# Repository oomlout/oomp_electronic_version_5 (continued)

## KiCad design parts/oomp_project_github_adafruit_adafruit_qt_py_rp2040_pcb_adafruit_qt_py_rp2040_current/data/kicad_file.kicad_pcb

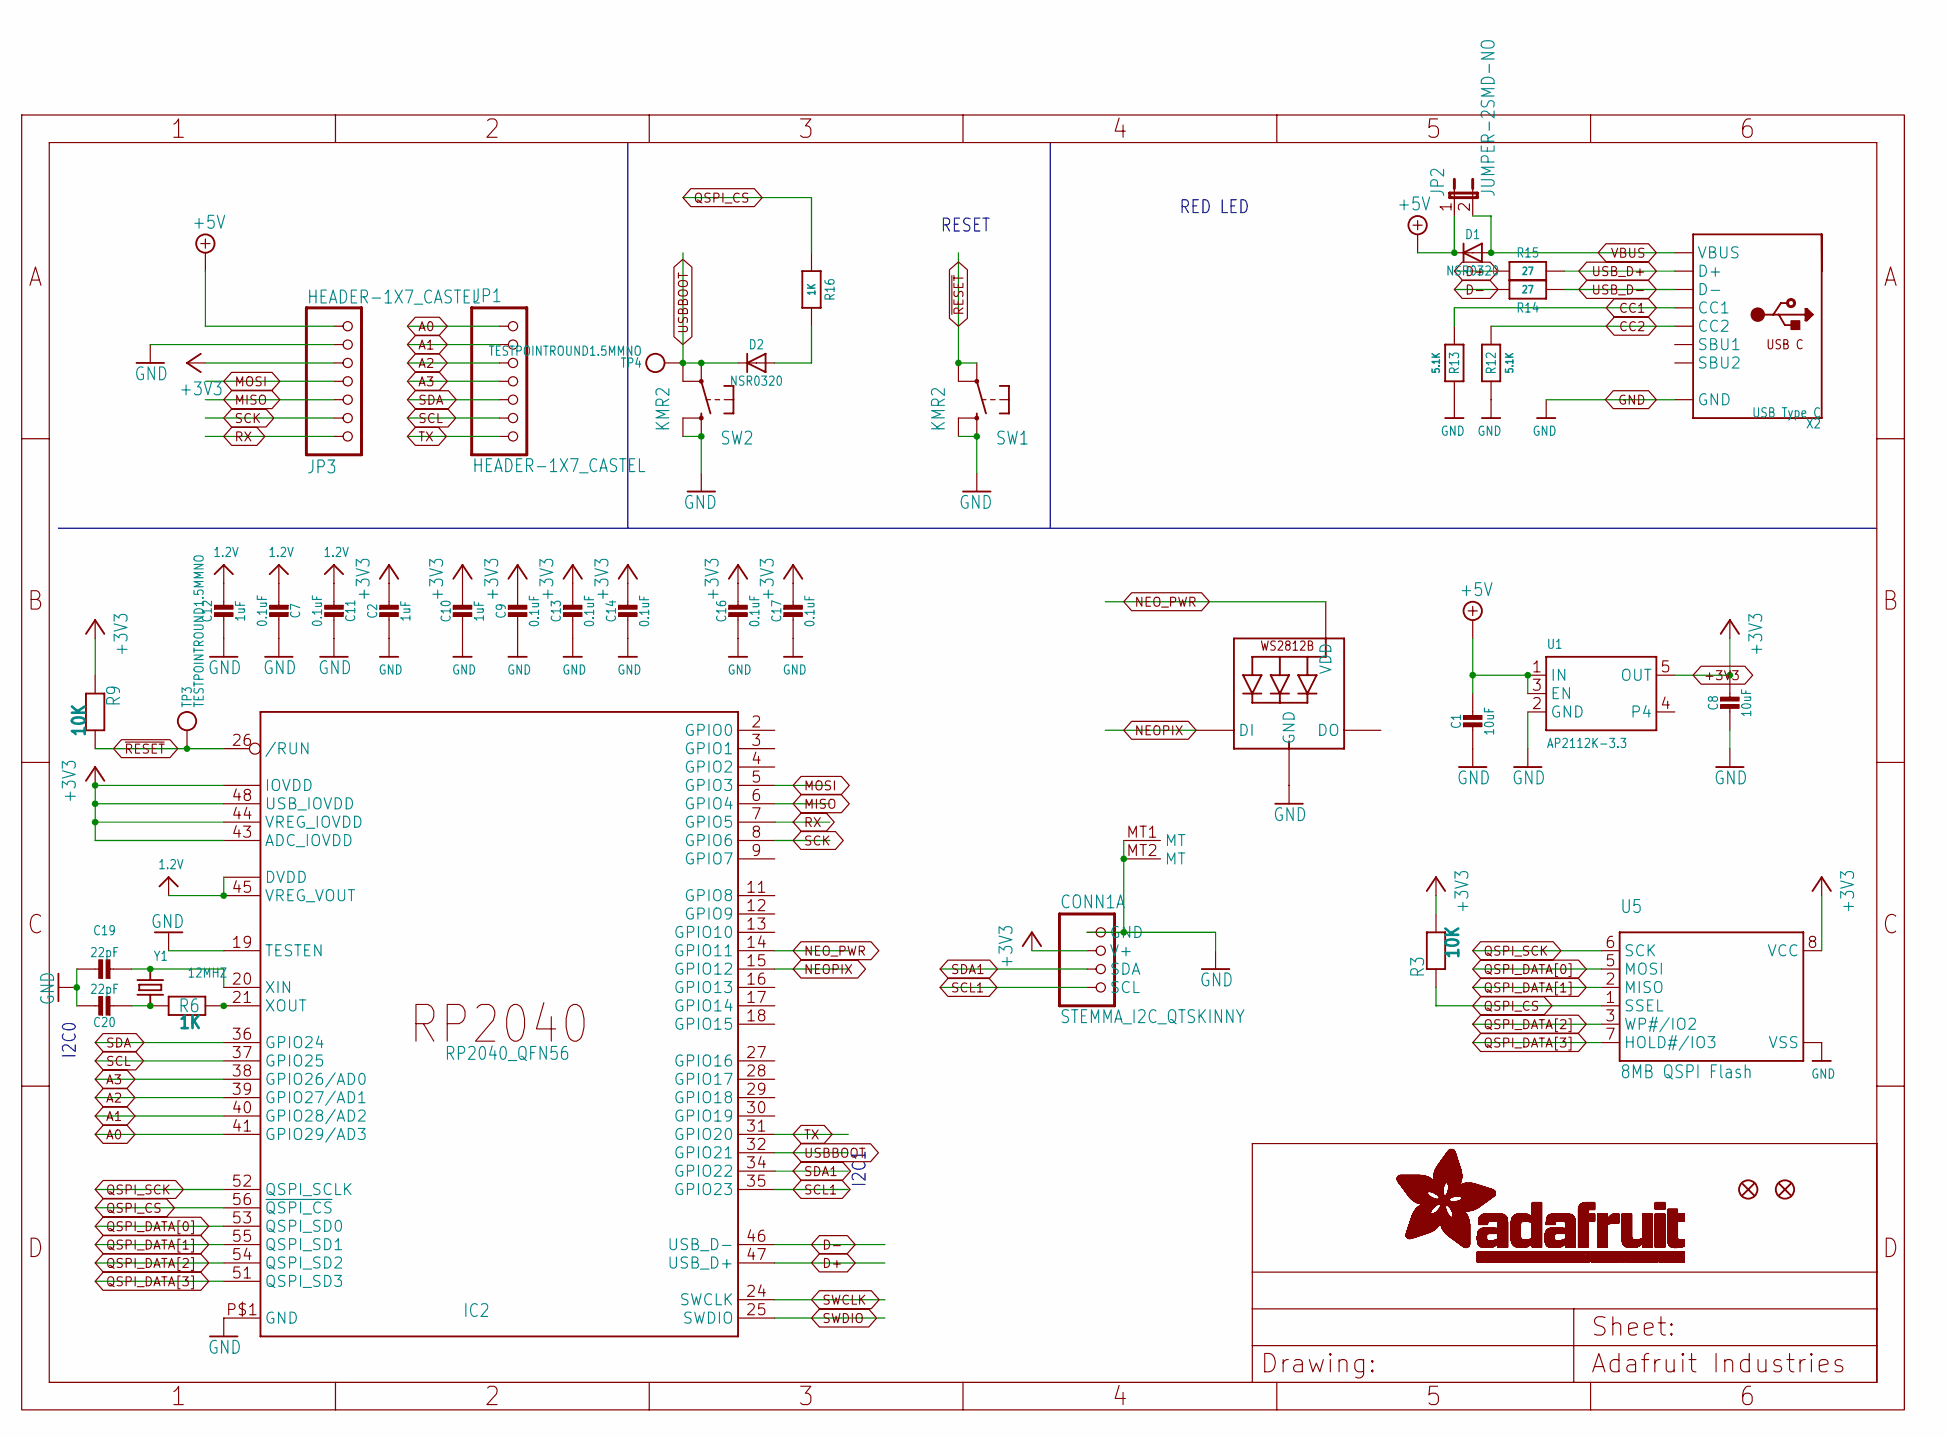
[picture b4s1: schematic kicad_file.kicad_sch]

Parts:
C1, C8: 10uF; 0805-NO
C2, C10, C12: 1uF; 0603-NO
C7, C9, C11, C13, C14, C16, C17: 0.1uF; _0402NO
C19, C20: 22pF; _0402NO
CONN1: STEMMA_I2C_QTSKINNY; JST_SH4_SKINNY
D1, D2: NSR0320; SOD-323_MINI
IC2: RP2040_QFN56; QFN56_7MM_REDUCEDEPAD
JP1, JP3: HEADER-1X7_CASTEL; 1X07_CASTEL
JP2: JUMPER-2SMD-NO; SJ_2S-NO
LED1: WS2812B_SK6805_1515; SK6805_1515
R3, R9: 10K; _0402NO
R6, R16: 1K; _0402NO
R12, R13: 5.1K; _0402NO
R14, R15: 27; _0402NO
SW1, SW2: KMR2; BTN_KMR2_4.6X2.8
TP3, TP4: TESTPOINTROUND1.5MMNO; TESTPOINT_ROUND_1.5MM_NO
U1: AP2112K-3.3; SOT23-5
U5: 8MB QSPI Flash; USON8_4X4
U$6, U$8: FIDUCIAL_1MM
X2: USB Type C; USB_C_CUSB31-CFM2AX-01-X
Y1: 12MHZ; CRYSTAL_2.5X2

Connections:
1.2V: C7.2, C11.2, C12.1, IC2.23 (DVDD), IC2.45 (VREG_VOUT), IC2.50 (DVDD)
+3V3: C2.1, C8.1, C9.1, C10.1, C13.1, C14.1, C16.1, C17.1, CONN1.2 (V+), IC2.1 (IOVDD), IC2.10 (IOVDD), IC2.22 (IOVDD), IC2.33 (IOVDD), IC2.42 (IOVDD), IC2.43 (ADC_IOVDD), IC2.44 (VREG_IOVDD), IC2.48 (USB_IOVDD), IC2.49 (IOVDD), JP3.5, JP3.5C (5), R3.2, R9.1, U1.5 (OUT), U5.8 (VCC)
+5V: C1.1, D1.C, JP2.1, JP3.7, JP3.7C (7), U1.1 (IN), U1.3 (EN)
A0: IC2.41 (GPIO29/AD3), JP1.1, JP1.1C (1)
A1: IC2.40 (GPIO28/AD2), JP1.2, JP1.2C (2)
A2: IC2.39 (GPIO27/AD1), JP1.3, JP1.3C (3)
A3: IC2.38 (GPIO26/AD0), JP1.4, JP1.4C (4)
CC1: R13.2, X2.A5 (CC1)
CC2: R12.2, X2.B5 (CC2)
D+: IC2.47 (USB_D+), R15.2
D-: IC2.46 (USB_D-), R14.2
GND: C1.2, C2.2, C7.1, C8.2, C9.2, C10.2, C11.1, C12.2, C13.2, C14.2, C16.2, C17.2, C19.1, C20.1, CONN1.1 (GND), CONN1.MT1 (MT), CONN1.MT2 (MT), IC2.19 (TESTEN), IC2.P$1 (GND), JP3.6, JP3.6C (6), LED1.4 (GND), R12.1, R13.1, SW1.B (S), SW1.B' (S1), SW2.B (S), SW2.B' (S1), U1.2 (GND), U5.4 (VSS), U5.PAD (VSS), X2.A1B12 (GND), X2.B1A12 (GND)
MISO: IC2.6 (GPIO4), JP3.3, JP3.3C (3)
MOSI: IC2.5 (GPIO3), JP3.4, JP3.4C (4)
unnamed: D2.A, R16.2
unnamed: C19.2, IC2.20 (XIN), Y1.3 (2)
unnamed: C20.2, R6.1, Y1.1
unnamed: IC2.21 (XOUT), R6.2
NEOPIX: IC2.15 (GPIO12), LED1.1 (DI)
NEO_PWR: IC2.14 (GPIO11), LED1.2 (VDD)
QSPI_CS: IC2.56 (~QSPI_CS), R3.1, R16.1, U5.1 (SSEL)
QSPI_DATA[0]: IC2.53 (QSPI_SD0), U5.5 (MOSI)
QSPI_DATA[1]: IC2.55 (QSPI_SD1), U5.2 (MISO)
QSPI_DATA[2]: IC2.54 (QSPI_SD2), U5.3 (WP#/IO2)
QSPI_DATA[3]: IC2.51 (QSPI_SD3), U5.7 (HOLD#/IO3)
QSPI_SCK: IC2.52 (QSPI_SCLK), U5.6 (SCK)
RX: IC2.7 (GPIO5), JP3.1, JP3.1C (1)
SCK: IC2.8 (GPIO6), JP3.2, JP3.2C (2)
SCL: IC2.37 (GPIO25), JP1.6, JP1.6C (6)
SCL1: CONN1.4 (SCL), IC2.35 (GPIO23)
SDA: IC2.36 (GPIO24), JP1.5, JP1.5C (5)
SDA1: CONN1.3 (SDA), IC2.34 (GPIO22)
SWCLK: IC2.24 (SWCLK)
SWDIO: IC2.25 (SWDIO)
TX: IC2.31 (GPIO20), JP1.7, JP1.7C (7)
USBBOOT: D2.C, IC2.32 (GPIO21), SW2.A, SW2.A' (P1), TP4.P$1
USB_D+: R15.1, X2.A6 (D+), X2.B6 (D+)
USB_D-: R14.1, X2.A7 (D-), X2.B7 (D-)
VBUS: D1.A, JP2.2, X2.A4B9 (VBUS), X2.B4A9 (VBUS)
~RESET: IC2.26 (/RUN), R9.2, SW1.A, SW1.A' (P1), TP3.P$1

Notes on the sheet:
I2C0
RESET
RED LED
I2C1

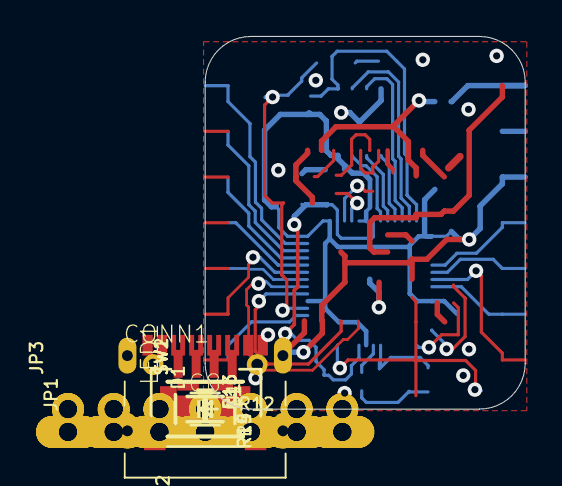
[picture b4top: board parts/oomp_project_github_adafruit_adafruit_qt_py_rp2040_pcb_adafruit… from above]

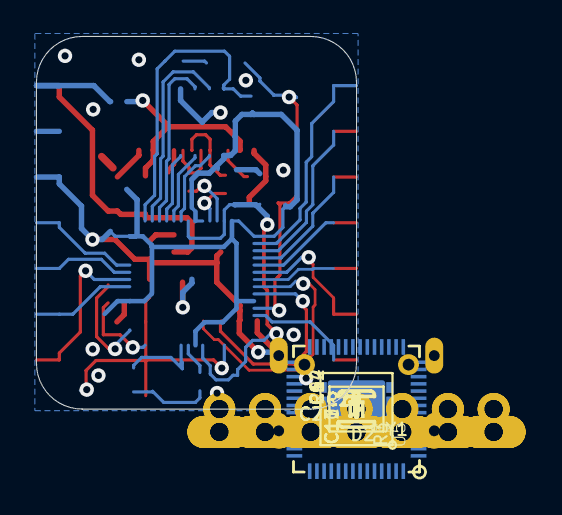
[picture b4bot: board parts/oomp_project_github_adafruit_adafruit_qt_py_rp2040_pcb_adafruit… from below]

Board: 16 copper layers, 17.8 x 20.7 mm, 42 parts (23 on the bottom side), 38 nets.

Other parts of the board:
U$1: QTPICO_BOT
U$2: QTPICO_TOP

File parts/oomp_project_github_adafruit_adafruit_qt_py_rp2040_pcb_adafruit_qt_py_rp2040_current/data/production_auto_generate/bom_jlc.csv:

Comment,Designator,Footprint,LCSC Part #
,"JP1,JP3",Adafruit QT Py RP2040-import-fps:1X07_CASTEL,C7501585
,U$1,Adafruit QT Py RP2040-import-fps:QTPICO_BOT,
,U$2,Adafruit QT Py RP2040-import-fps:QTPICO_TOP,
,JP2,Adafruit QT Py RP2040-import-fps:SJ_2S-NO,
,"TP3,TP4",Adafruit QT Py RP2040-import-fps:TESTPOINT_ROUND_1.5MM_NO,
  NSR0320,"D1,D2",Adafruit QT Py RP2040-import-fps:SOD-323_MINI,
0.1uF,"C7,C9,C11,C13,C14,C16,C17",Adafruit QT Py RP2040-import-fps:_0402NO,C60474
10K,"R3,R9",Adafruit QT Py RP2040-import-fps:_0402NO,C2906861
10uF,"C1,C8",Adafruit QT Py RP2040-import-fps:0805-NO,
12MHZ,Y1,Adafruit QT Py RP2040-import-fps:CRYSTAL_2.5X2,
1K,"R6,R16",Adafruit QT Py RP2040-import-fps:_0402NO,C2906864
1uF,"C2,C10,C12",Adafruit QT Py RP2040-import-fps:0603-NO,C5673
22pF,"C19,C20",Adafruit QT Py RP2040-import-fps:_0402NO,C106203
27,"R14,R15",Adafruit QT Py RP2040-import-fps:_0402NO,C25100
5.1K,"R12,R13",Adafruit QT Py RP2040-import-fps:_0402NO,C25905
8MB QSPI Flash,U5,Adafruit QT Py RP2040-import-fps:USON8_4X4,
AP2112K-3.3,U1,Adafruit QT Py RP2040-import-fps:SOT23-5,
FIDUCIAL_1MM,"U$6,U$8",Adafruit QT Py RP2040-import-fps:FIDUCIAL_1MM,
KMR2,"SW1,SW2",Adafruit QT Py RP2040-import-fps:BTN_KMR2_4.6X2.8,
RP2040_QFN56,IC2,Adafruit QT Py RP2040-import-fps:QFN56_7MM_REDUCEDEPAD,
STEMMA_I2C_QTSKINNY,CONN1,Adafruit QT Py RP2040-import-fps:JST_SH4_SKINNY,
USB Type C,X2,Adafruit QT Py RP2040-import-fps:USB_C_CUSB31-CFM2AX-01-X,
WS2812B_SK6805_1515,LED1,Adafruit QT Py RP2040-import-fps:SK6805_1515,

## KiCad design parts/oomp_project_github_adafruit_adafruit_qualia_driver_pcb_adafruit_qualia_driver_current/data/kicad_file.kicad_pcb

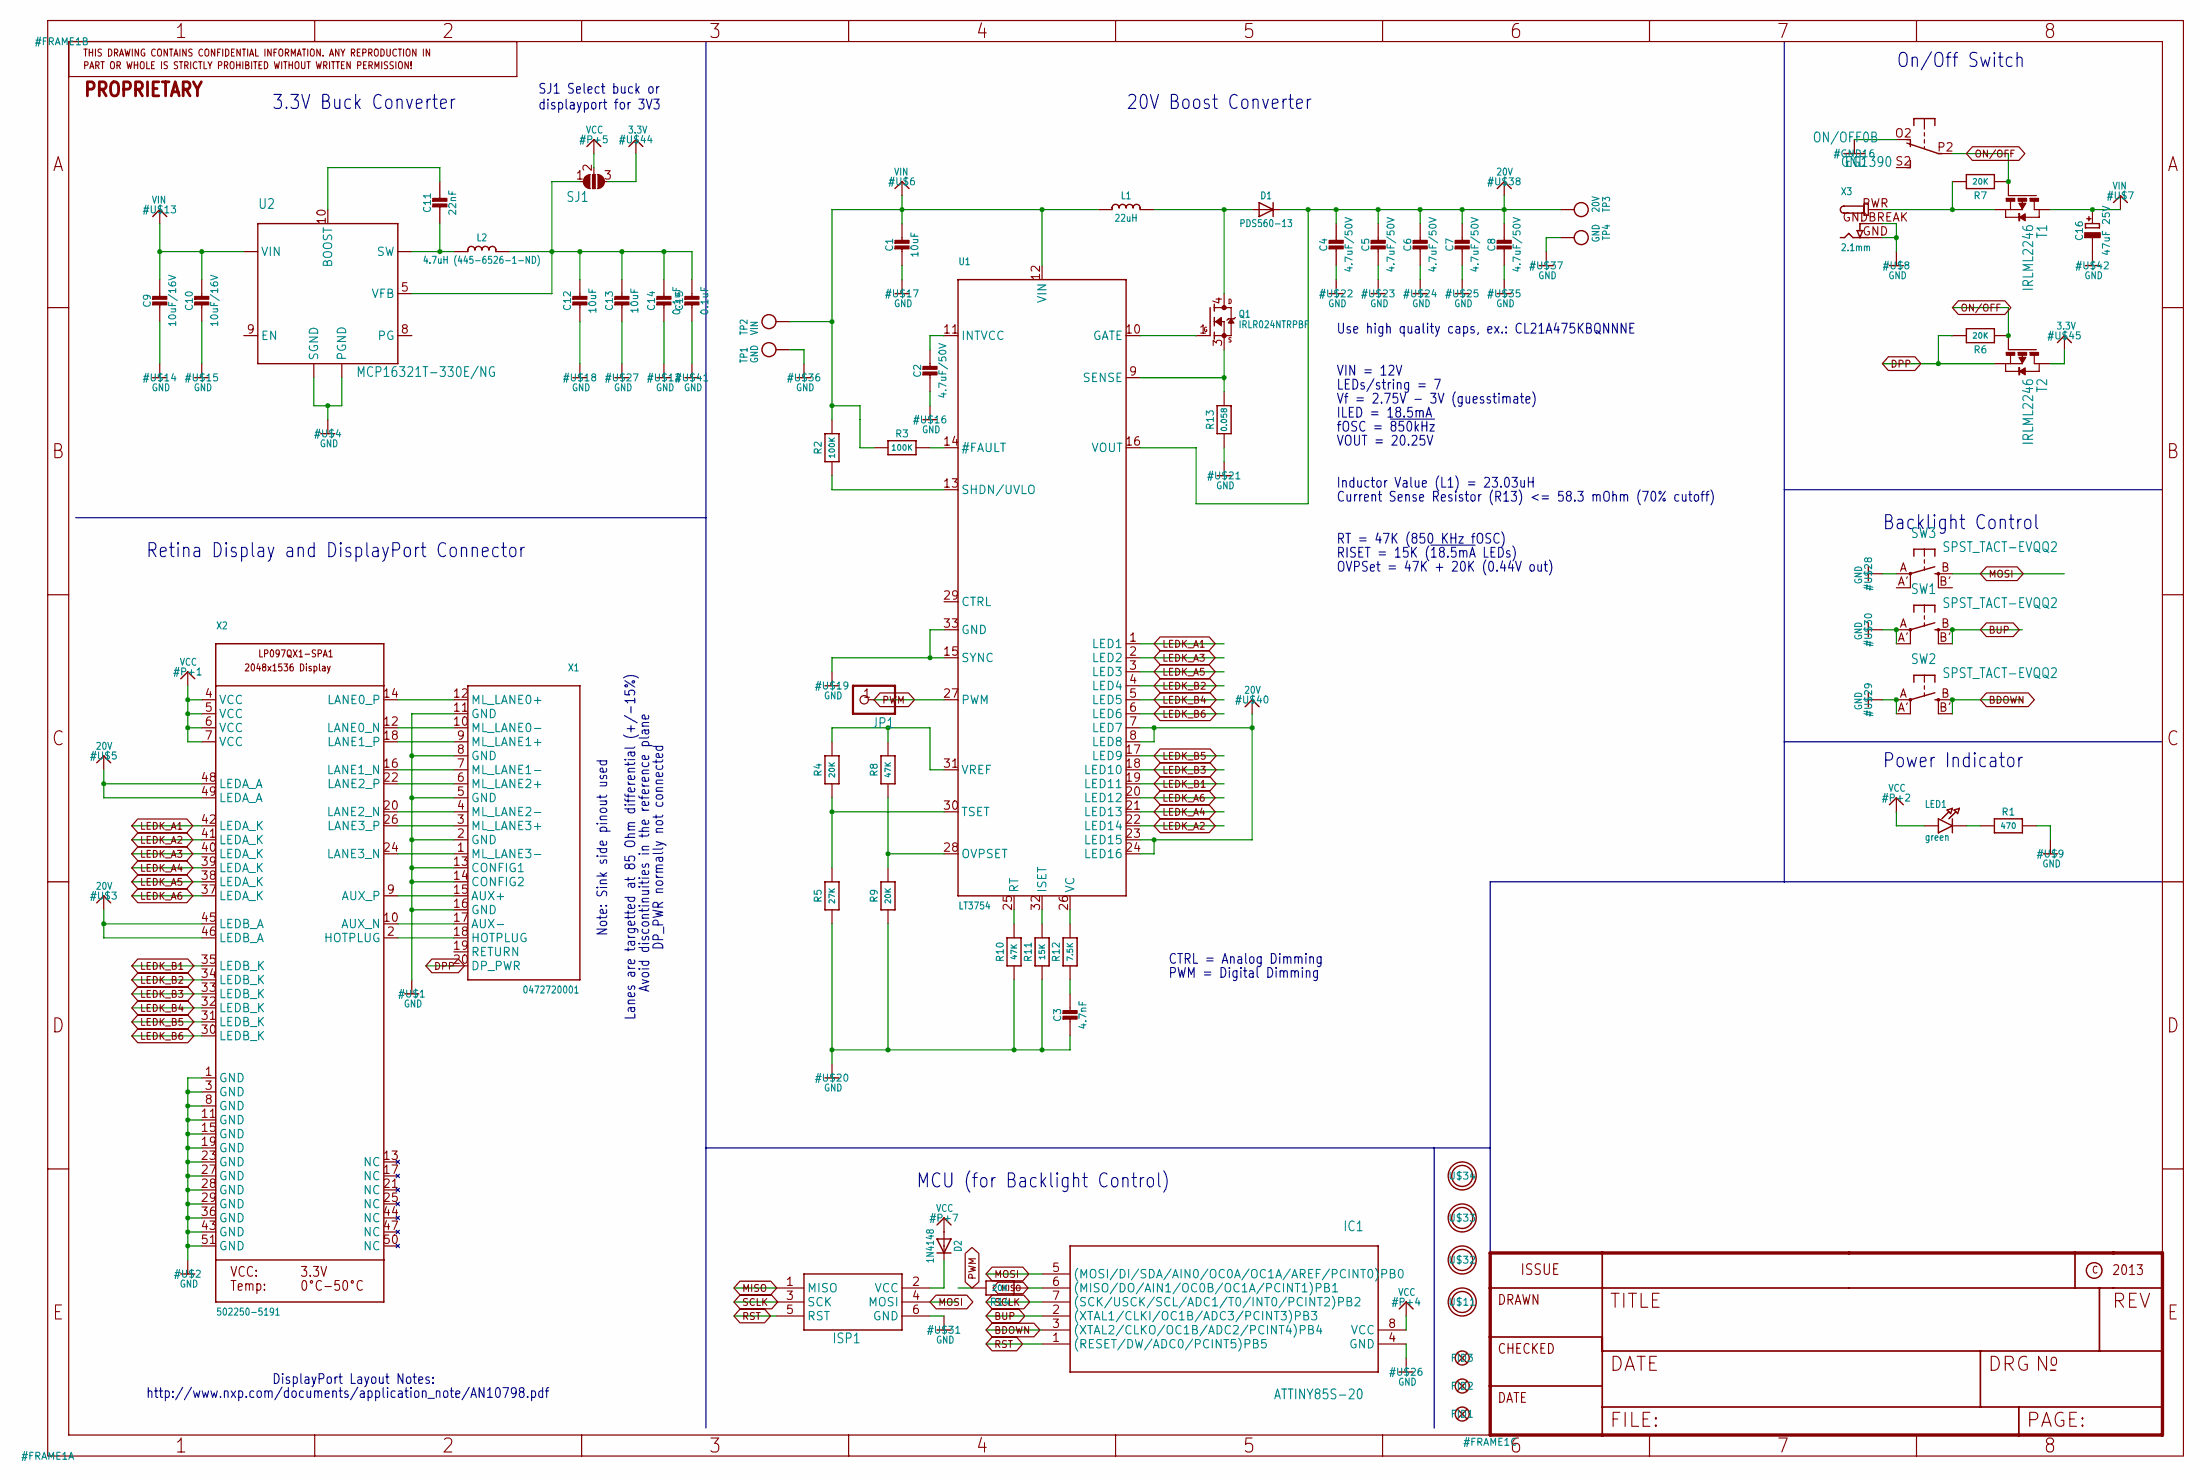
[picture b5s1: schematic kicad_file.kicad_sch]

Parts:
C1, C12, C13: 10uF; _0805
C2, C4, C5, C6, C7, C8: 4.7uF/50V; _0805
C3: 4.7nF; _0805
C9, C10: 10uF/16V; _0805
C11: 22nF; _0805
C14, C15: 0.1uF; _0805
C16: 47uF 25V; PANASONIC_C
D1: PDS560-13; POWERDI-5
D2: 1N4148; SOD-323
FID1, FID2, FID3: FIDUCIAL""; FIDUCIAL_1MM
IC1: ATTINY85S-20; SOIC8
ISP1: AVRISP-6; AVRISP
JP1: PINHD-1X1CB; 1X01-CLEANBIG
L1: 22uH; INDUCTOR_6X6MM_SUMIDA_CDRH5D28
L2: 4.7uH (445-6526-1-ND); INDUCTOR_5X5MM_TDK_VLC5045
LED1: green; CHIPLED_0805
ON/OFF0: EG1390
Q1: IRLR024NTRPBF; DPAK
R1: 470; _0805
R2, R3: 100K; _0805
R4, R9, R14: 20K; _0805
R5: 27K; _0805
R6, R7: 20K; _0805MP
R8, R10: 47K; _0805
R11: 15K; _0805
R12: 7.5K; _0805
R13: 0.058; 2512
SJ1: SOLDERJUMPER_2WAY; SOLDERJUMPER_2WAY_OPEN_NOPASTE
SW1, SW2, SW3: SPST_TACT-EVQQ2; EVQ-Q2
T1, T2: IRLML2246; SOT-23
TP1, TP4: GND; TESTPOINT_ROUND_1MM
TP2: VIN; TESTPOINT_ROUND_1MM
TP3: 20V; TESTPOINT_ROUND_1MM
U1: LT3754; QFN32_5MM
U2: MCP16321T-330E/NG; QFN16_3MM
U$11, U$32, U$33, U$34: MOUNTINGHOLE3.0THIN; MOUNTINGHOLE_3.0_PLATEDTHIN
X1: 0472720001; DISPLAYPORT_0472720001
X2: 502250-5191; FPC_51PIN_502250-5191_EXT
X3: 2.1mm; DCJACK_2MM_SMT

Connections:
3.3V: SJ1.3, T2.1 (D)
20V: C4.1, C5.1, C6.1, C7.1, C8.1, D1.C, TP3.P$1, U1.7 (LED7), U1.8 (LED8), U1.16 (VOUT), U1.23 (LED15), U1.24 (LED16), X2.45 (LEDB_A), X2.46 (LEDB_A), X2.48 (LEDA_A), X2.49 (LEDA_A)
AUX+: X1.15 (AUX+), X2.9 (AUX_P)
AUX-: X1.17 (AUX-), X2.10 (AUX_N)
BDOWN: IC1.3 ((XTAL2/CLKO/OC1B/ADC2/PCINT4)PB4), SW2.B (S), SW2.B' (S1)
BUP: IC1.2 ((XTAL1/CLKI/OC1B/ADC3/PCINT3)PB3), SW1.B (S), SW1.B' (S1)
DPP: R6.2, T2.2 (S), X1.20 (DP_PWR)
GND: C1.2, C2.2, C3.2, C4.2, C5.2, C6.2, C7.2, C8.2, C9.2, C10.2, C12.2, C13.2, C14.2, C15.2, C16.-, IC1.4 (GND), ISP1.6 (GND), ON/OFF0.O2 (O), R1.2, R5.1, R9.1, R10.1, R11.1, R13.1, SW1.A, SW1.A' (P1), SW2.A, SW2.A' (P1), SW3.A, TP1.P$1, TP4.P$1, U1.15 (SYNC), U1.33 (GND), U2.4 (SGND), U2.14 (PGND), U2.15 (PGND), U2.THERMAL (SGND), X1.2 (GND), X1.5 (GND), X1.8 (GND), X1.11 (GND), X1.13 (CONFIG1), X1.14 (CONFIG2), X1.16 (GND), X2.1 (GND), X2.3 (GND), X2.8 (GND), X2.11 (GND), X2.15 (GND), X2.19 (GND), X2.23 (GND), X2.27 (GND), X2.28 (GND), X2.29 (GND), X2.36 (GND), X2.43 (GND), X2.51 (GND), X3.GND, X3.GNDBREAK
HOTPLUG: X1.18 (HOTPLUG), X2.2 (HOTPLUG)
LEDK_A1: U1.1 (LED1), X2.42 (LEDA_K)
LEDK_A2: U1.22 (LED14), X2.41 (LEDA_K)
LEDK_A3: U1.2 (LED2), X2.40 (LEDA_K)
LEDK_A4: U1.21 (LED13), X2.39 (LEDA_K)
LEDK_A5: U1.3 (LED3), X2.38 (LEDA_K)
LEDK_A6: U1.20 (LED12), X2.37 (LEDA_K)
LEDK_B1: U1.19 (LED11), X2.35 (LEDB_K)
LEDK_B2: U1.4 (LED4), X2.34 (LEDB_K)
LEDK_B3: U1.18 (LED10), X2.33 (LEDB_K)
LEDK_B4: U1.5 (LED5), X2.32 (LEDB_K)
LEDK_B5: U1.17 (LED9), X2.31 (LEDB_K)
LEDK_B6: U1.6 (LED6), X2.30 (LEDB_K)
MISO: IC1.6 ((MISO/DO/AIN1/OC0B/OC1A/PCINT1)PB1), ISP1.1 (MISO), R14.1
MOSI: IC1.5 ((MOSI/DI/SDA/AIN0/OC0A/OC1A/AREF/PCINT0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), ISP1.4 (MOSI), SW3.B (S)
unnamed: X1.12 (ML_LANE0+), X2.14 (LANE0_P)
unnamed: X1.10 (ML_LANE0-), X2.12 (LANE0_N)
unnamed: X1.9 (ML_LANE1+), X2.18 (LANE1_P)
unnamed: X1.7 (ML_LANE1-), X2.16 (LANE1_N)
unnamed: X1.6 (ML_LANE2+), X2.22 (LANE2_P)
unnamed: X1.4 (ML_LANE2-), X2.20 (LANE2_N)
unnamed: X1.3 (ML_LANE3+), X2.26 (LANE3_P)
unnamed: X1.1 (ML_LANE3-), X2.24 (LANE3_N)
unnamed: C2.1, U1.11 (INTVCC)
unnamed: R2.1, U1.13 (SHDN/UVLO)
unnamed: R3.2, U1.14 (#FAULT)
unnamed: R12.2, U1.26 (VC)
unnamed: C3.1, R12.1
unnamed: LED1.C, R1.1
unnamed: R4.1, R5.2, U1.30 (TSET)
unnamed: R4.2, R8.2, U1.31 (VREF)
unnamed: R7.2, T1.2 (S), X3.PWR
unnamed: R8.1, R9.2, U1.28 (OVPSET)
unnamed: R10.2, U1.25 (RT)
unnamed: D2.C, ISP1.2 (VCC)
unnamed: R11.2, U1.32 (ISET)
unnamed: Q1.3 (S), R13.2, U1.9 (SENSE)
unnamed: Q1.1 (G), U1.10 (GATE)
unnamed: D1.A1 (A), D1.A2 (A), L1.P$2 (2), Q1.4 (D)
unnamed: C12.1, C13.1, C14.1, C15.1, L2.P$2 (2), SJ1.1, U2.5 (VFB)
unnamed: C11.1, U2.10 (BOOST)
unnamed: C11.2, L2.P$1 (1), U2.1 (SW), U2.12 (SW), U2.13 (SW), U2.16 (SW)
ON/OFF: ON/OFF0.P2, R6.1, R7.1, T1.3 (G), T2.3 (G)
PWM: JP1.1, R14.2, U1.27 (PWM)
RST: IC1.1 ((RESET/DW/ADC0/PCINT5)PB5), ISP1.5 (RST)
SCLK: IC1.7 ((SCK/USCK/SCL/ADC1/T0/INT0/PCINT2)PB2), ISP1.3 (SCK)
VCC: D2.A, IC1.8 (VCC), LED1.A, SJ1.2, X2.4 (VCC), X2.5 (VCC), X2.6 (VCC), X2.7 (VCC)
VIN: C1.1, C9.1, C10.1, C16.+, L1.P$1 (1), R2.2, R3.1, T1.1 (D), TP2.P$1, U1.12 (VIN), U2.2 (VIN), U2.3 (VIN), U2.11 (VIN)

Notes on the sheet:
OVPSet = 47K + 20K (0.44V out)
VIN = 12V
RISET = 15K (~{18.5mA} LEDs)
ILED = 18.5mA
Note: Sink side pinout used~{}
20V Boost Converter
DP_PWR normally not connected
http://www.nxp.com/documents/application_note/AN10798.pdf
MCU (for Backlight Control)
Use high quality caps, ex.: CL21A475KBQNNNE
DisplayPort Layout Notes:
PWM = Digital Dimming
Current Sense Resistor (R13) <= 58.3 mOhm (70% cutoff)
Avoid discontinuities in the reference plane
Lanes are targetted at 85 Ohm differential (+/-15%)
VOUT = 20.25V
Inductor Value (L1) = 23.03uH
3.3V Buck Converter
SJ1 Select buck or displayport for 3V3
On/Off Switch
RT = 47K (850 KHz fOSC)
Backlight Control
CTRL = Analog Dimming
Retina Display and DisplayPort Connector
Power Indicator
fOSC = ~{850kHz}
LEDs/string = 7
Vf = 2.75V - 3V (guesstimate)

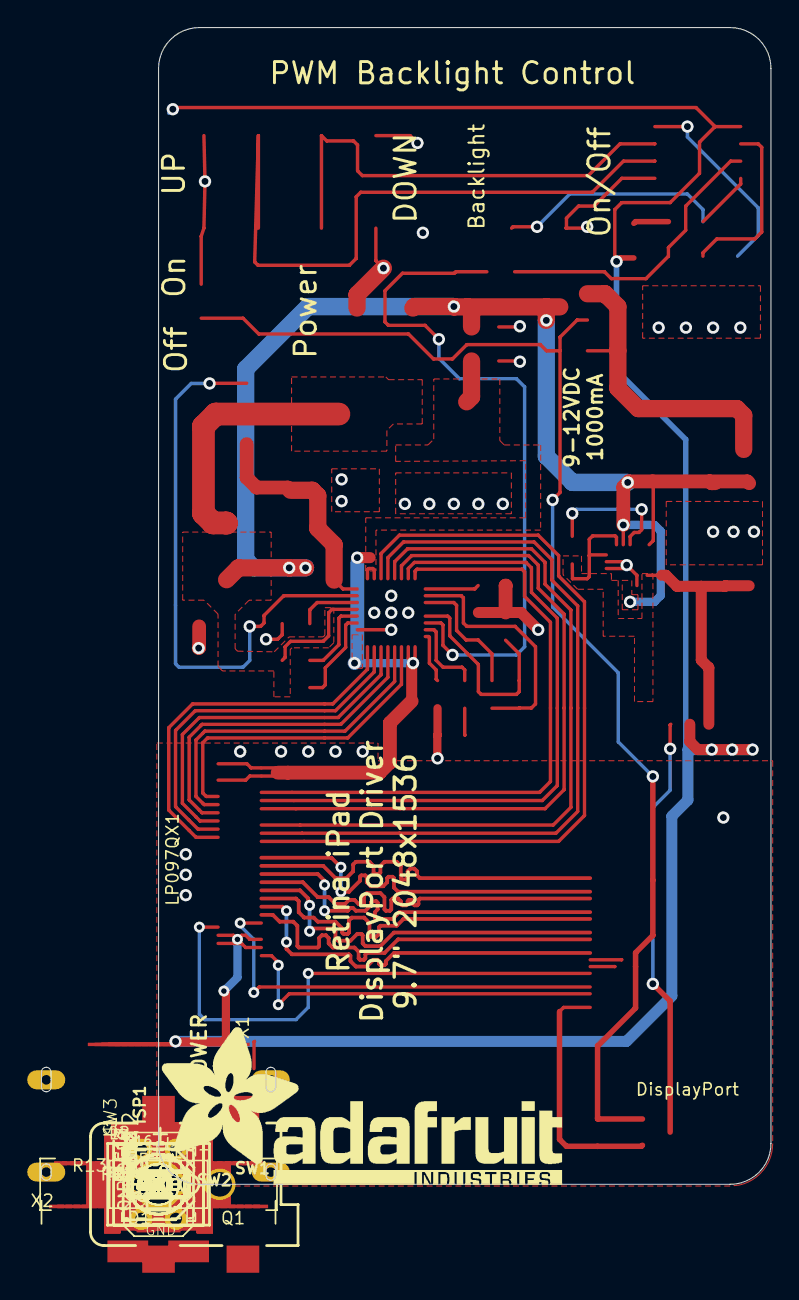
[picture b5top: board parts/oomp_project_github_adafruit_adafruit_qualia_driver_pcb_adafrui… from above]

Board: 2 copper layers, 45.0 x 85.0 mm, 64 parts (0 on the bottom side), 56 nets.

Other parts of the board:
U$10: SYMBOL_POSITIVE_CENTER-M
U$39: ADAFRUIT_TEXT_30MM

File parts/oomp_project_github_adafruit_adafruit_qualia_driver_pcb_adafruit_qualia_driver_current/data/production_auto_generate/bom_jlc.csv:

Comment,Designator,Footprint,LCSC Part #
,JP1,Adafruit Qualia Driver-import-fps:1X01-CLEANBIG,C7501259
,U$39,Adafruit Qualia Driver-import-fps:ADAFRUIT_TEXT_30MM,
,U$10,Adafruit Qualia Driver-import-fps:SYMBOL_POSITIVE_CENTER-M,
0.058,R13,Adafruit Qualia Driver-import-fps:2512,
0.1uF,"C14,C15",Adafruit Qualia Driver-import-fps:_0805,
0472720001,X1,Adafruit Qualia Driver-import-fps:DISPLAYPORT_0472720001,
100K,"R2,R3",Adafruit Qualia Driver-import-fps:_0805,C149504
10uF,"C1,C12,C13",Adafruit Qualia Driver-import-fps:_0805,
10uF/16V,"C9,C10",Adafruit Qualia Driver-import-fps:_0805,
15K,R11,Adafruit Qualia Driver-import-fps:_0805,C2930170
1N4148,D2,Adafruit Qualia Driver-import-fps:SOD-323,
2.1mm,X3,Adafruit Qualia Driver-import-fps:DCJACK_2MM_SMT,
20K,"R4,R9,R14",Adafruit Qualia Driver-import-fps:_0805,
20K,"R6,R7",Adafruit Qualia Driver-import-fps:_0805MP,
20V,TP3,Adafruit Qualia Driver-import-fps:TESTPOINT_ROUND_1MM,
22nF,C11,Adafruit Qualia Driver-import-fps:_0805,
22uH,L1,Adafruit Qualia Driver-import-fps:INDUCTOR_6X6MM_SUMIDA_CDRH5D28,
27K,R5,Adafruit Qualia Driver-import-fps:_0805,C2907247
4.7nF,C3,Adafruit Qualia Driver-import-fps:_0805,
4.7uF/50V,"C2,C4,C5,C6,C7,C8",Adafruit Qualia Driver-import-fps:_0805,
4.7uH (445-6526-1-ND),L2,Adafruit Qualia Driver-import-fps:INDUCTOR_5X5MM_TDK_VLC5045,
470,R1,Adafruit Qualia Driver-import-fps:_0805,C17710
47K,"R8,R10",Adafruit Qualia Driver-import-fps:_0805,C17713
47uF 25V,C16,Adafruit Qualia Driver-import-fps:PANASONIC_C,
502250-5191,X2,Adafruit Qualia Driver-import-fps:FPC_51PIN_502250-5191_EXT,
7.5K,R12,Adafruit Qualia Driver-import-fps:_0805,C17807
ATTINY85-20S,IC1,Adafruit Qualia Driver-import-fps:SOIC8,
AVRISP-6,ISP1,Adafruit Qualia Driver-import-fps:AVRISP,
EG1390,ON/OFF0,Adafruit Qualia Driver-import-fps:EG1390,
GND,"TP1,TP4",Adafruit Qualia Driver-import-fps:TESTPOINT_ROUND_1MM,
green,LED1,Adafruit Qualia Driver-import-fps:CHIPLED_0805,
IRLML2246,"T1,T2",Adafruit Qualia Driver-import-fps:SOT-23,
IRLR024NTRPBF,Q1,Adafruit Qualia Driver-import-fps:DPAK,
LT3754,U1,Adafruit Qualia Driver-import-fps:QFN32_5MM,
MCP16321T-330E/NG ,U2,Adafruit Qualia Driver-import-fps:QFN16_3MM,
PDS560-13,D1,Adafruit Qualia Driver-import-fps:POWERDI-5,
SPST_TACT-EVQQ2,"SW1,SW2,SW3",Adafruit Qualia Driver-import-fps:EVQ-Q2,
VIN,TP2,Adafruit Qualia Driver-import-fps:TESTPOINT_ROUND_1MM,

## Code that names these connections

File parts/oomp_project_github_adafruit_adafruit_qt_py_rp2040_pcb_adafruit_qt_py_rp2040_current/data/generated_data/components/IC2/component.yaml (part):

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        pin_number: '8'
        pin_name: VCC
    - number: '2'
      name: GPIO0
      electrical_type: bidirectional
      graphic_style: line
      local_position:
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      no_connect: false
      connected_to: []
    - number: '3'
      name: GPIO1
      electrical_type: bidirectional
      graphic_style: line
      local_position:
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      no_connect: false
      connected_to: []
    - number: '4'
      name: GPIO2
      electrical_type: bidirectional
      graphic_style: line
      local_position:
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      no_connect: false
      connected_to: []
    - number: '5'
      name: GPIO3
      electrical_type: bidirectional
      graphic_style: line
      local_position:
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        pin_number: 4C
        pin_name: '4'
    - number: '6'
      name: GPIO4
      electrical_type: bidirectional
      graphic_style: line
      local_position:
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        pin_number: 3C
        pin_name: '3'
    - number: '7'
      name: GPIO5
      electrical_type: bidirectional
      graphic_style: line
      local_position:
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        pin_number: 1C
        pin_name: '1'
    - number: '8'
      name: GPIO6
      electrical_type: bidirectional
      graphic_style: line
      local_position:
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        pin_number: 2C
        pin_name: '2'
    - number: '9'
      name: GPIO7
      electrical_type: bidirectional
      graphic_style: line
      local_position:
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        pin_number: '8'
        pin_name: VCC
    - number: '11'
      name: GPIO8
      electrical_type: bidirectional
      graphic_style: line
      local_position:
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      no_connect: false
      connected_to: []
    - number: '12'
      name: GPIO9
      electrical_type: bidirectional
      graphic_style: line
      local_position:
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      no_connect: false
      connected_to: []
    - number: '13'
      name: GPIO10
      electrical_type: bidirectional
      graphic_style: line
      local_position:
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      no_connect: false
      connected_to: []
    - number: '14'
      name: GPIO11
      electrical_type: bidirectional
      graphic_style: line
      local_position:
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        pin_number: '2'
        pin_name: VDD
    - number: '15'
      name: GPIO12
      electrical_type: bidirectional
      graphic_style: line
      local_position:
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      no_connect: false
      connected_to: []
    - number: '29'
      name: GPIO18
      electrical_type: bidirectional
      graphic_style: line
      local_position:
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      no_connect: false
      connected_to: []
    - number: '30'
      name: GPIO19
      electrical_type: bidirectional
      graphic_style: line
      local_position:
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      no_connect: false
      connected_to: []
    - number: '31'
      name: GPIO20
      electrical_type: bidirectional
      graphic_style: line
      local_position:
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        pin_number: 7C
        pin_name: '7'
    - number: '32'
      name: GPIO21
      electrical_type: bidirectional
      graphic_style: line
      local_position:
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        pin_number: '8'
        pin_name: VCC
    - number: '34'
      name: GPIO22
      electrical_type: bidirectional
      graphic_style: line
      local_position:
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        pin_number: '3'
        pin_name: SDA
    - number: '35'
      name: GPIO23
      electrical_type: bidirectional
      graphic_style: line
      local_position:
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        pin_number: '4'
        pin_name: SCL
    - number: '36'
      name: GPIO24
      electrical_type: bidirectional
      graphic_style: line
      local_position:
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        pin_number: 5C
        pin_name: '5'
    - number: '37'
      name: GPIO25
      electrical_type: bidirectional
      graphic_style: line
      local_position:
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        pin_number: 6C
        pin_name: '6'
    - number: '38'
      name: GPIO26/AD0
      electrical_type: bidirectional
      graphic_style: line
      local_position:
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        pin_number: 4C
        pin_name: '4'
    - number: '39'
      name: GPIO27/AD1
      electrical_type: bidirectional
      graphic_style: line
      local_position:
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        pin_number: 3C
        pin_name: '3'
    - number: '40'
      name: GPIO28/AD2
      electrical_type: bidirectional
      graphic_style: line
      local_position:
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        pin_number: 2C
        pin_name: '2'
    - number: '41'
      name: GPIO29/AD3
      electrical_type: bidirectional
      graphic_style: line
      local_position:
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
